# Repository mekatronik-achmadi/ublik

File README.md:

# ublik

Hello everybody out there

I’m doing a free customizable and developer-friendly mini Solar Home System (just a hobby, won’t be big and
professional like many vendors nowadays) 

I’d like any feedback on things people who understand how Solar Home System supposed to be

I call this project as Ublik. This name come from traditional oil lamp used in my country before modern electric lamp replaced it

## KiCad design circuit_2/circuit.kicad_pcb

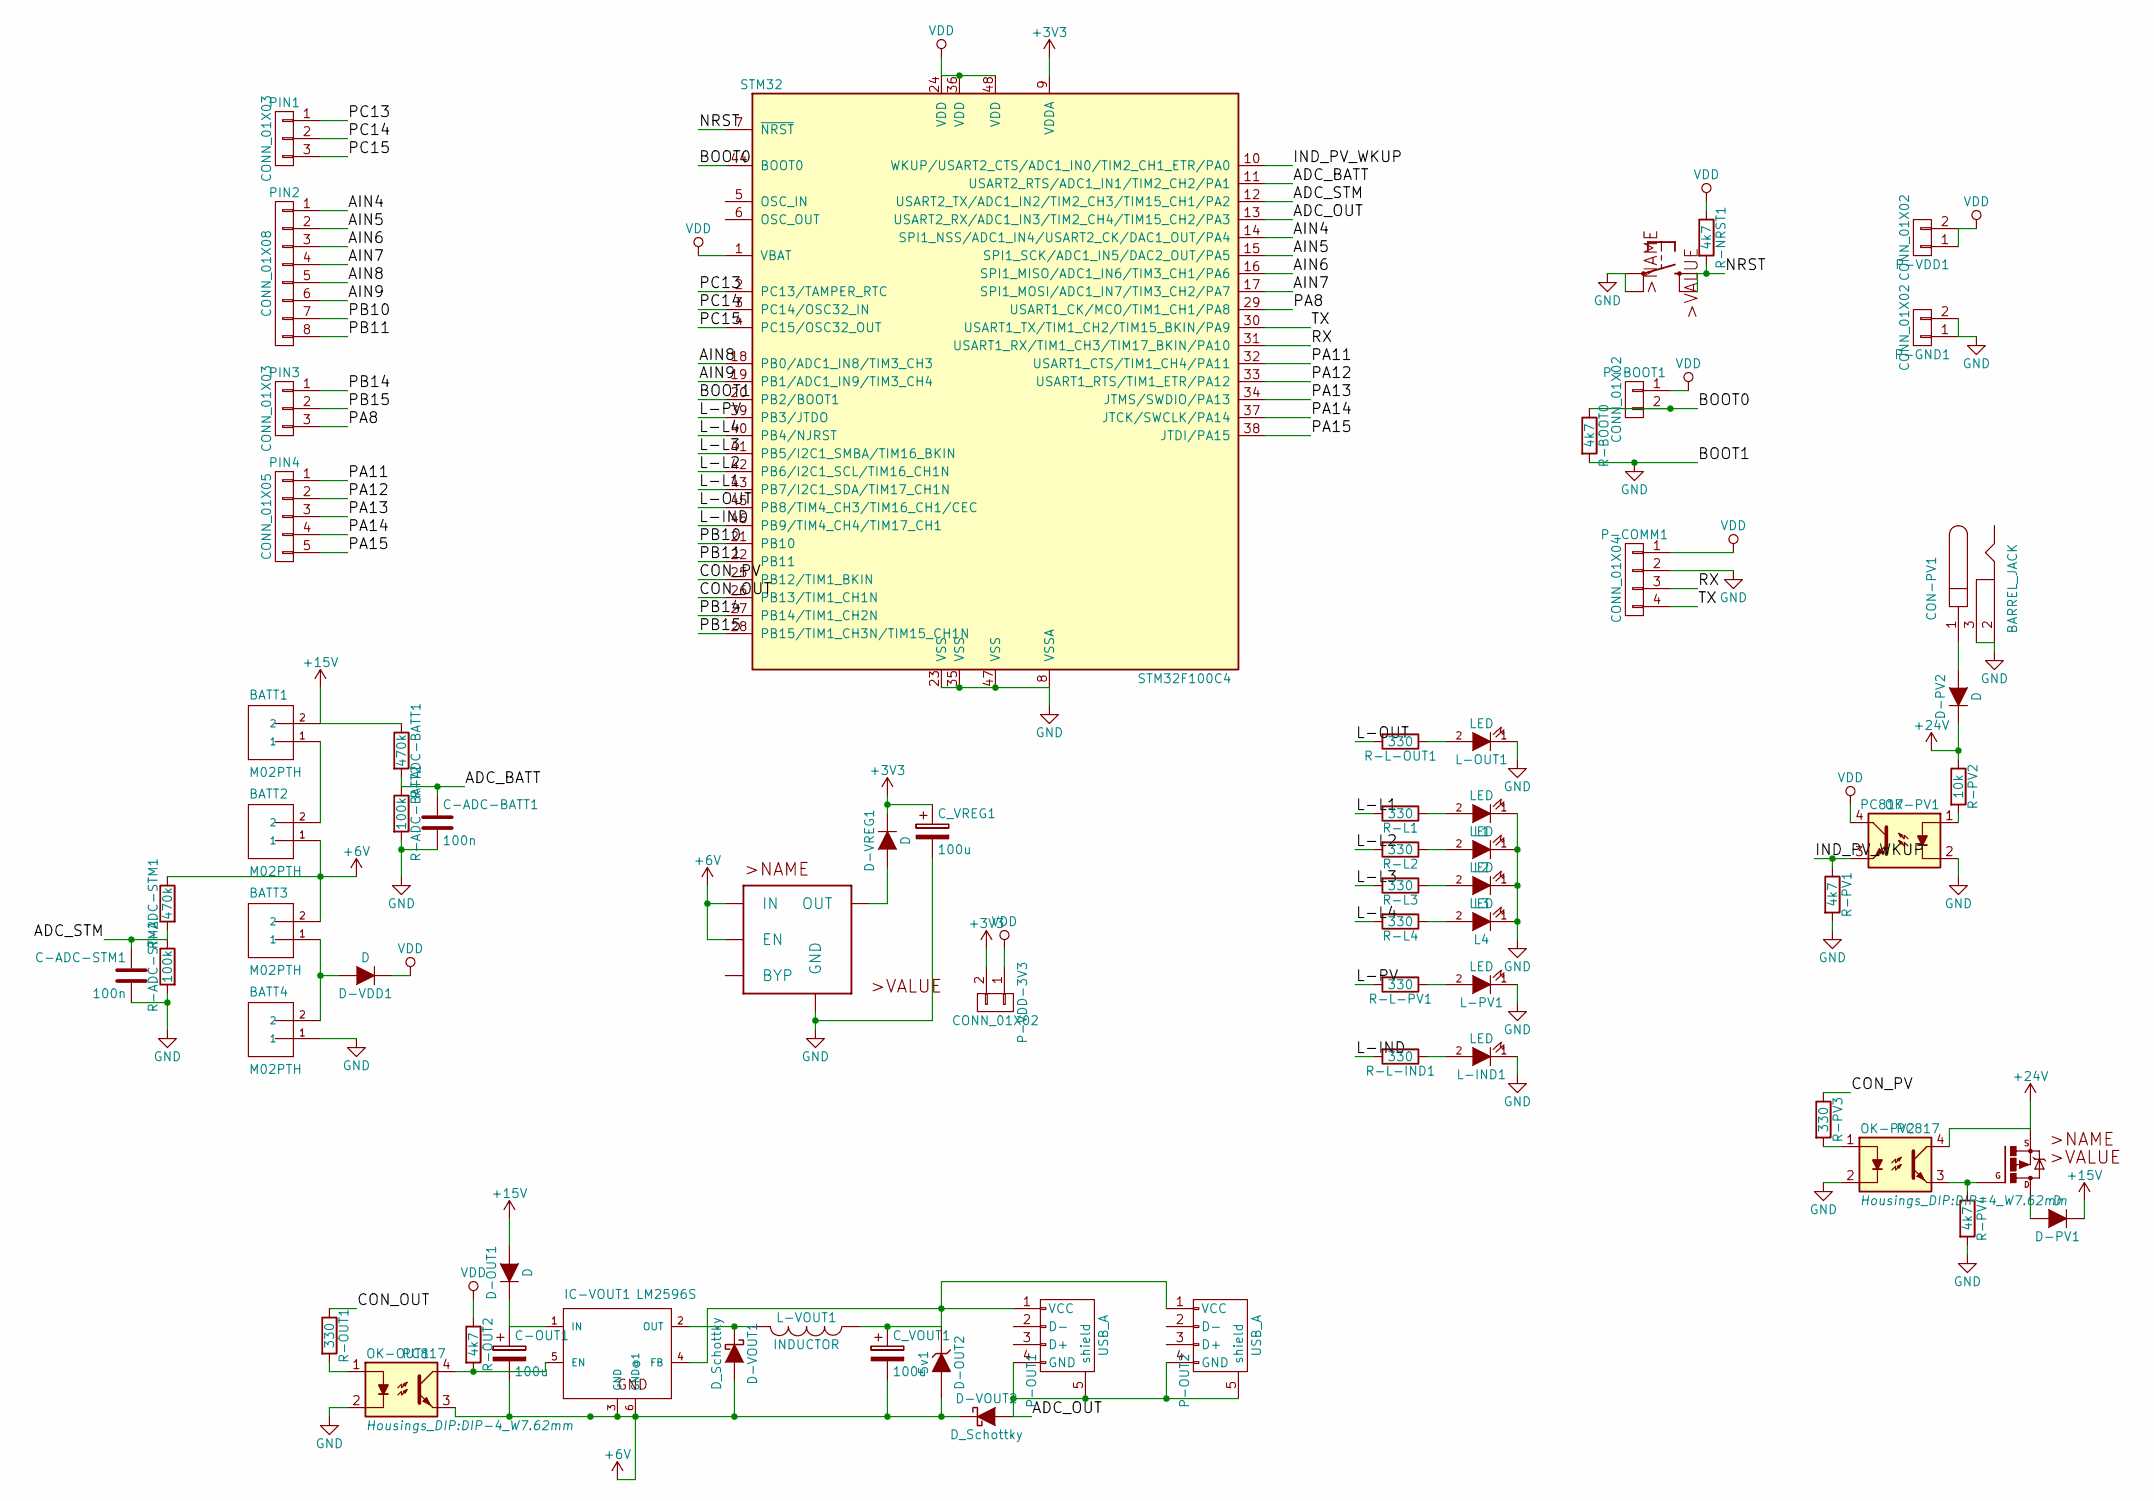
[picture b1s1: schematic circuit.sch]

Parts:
BATT1, BATT2, BATT3, BATT4: M02PTH; SparkFun-1X02_XTRA_BIG
C-ADC-BATT1: 100n; C_0805_HandSoldering
C-ADC-STM1: 100n; C_0805_HandSoldering
C-OUT1: 100u; C_Radial_D5_L6_P2.5
CON-PV1: BARREL_JACK; JACK_ALIM
C_VOUT1: 100u; C_Radial_D5_L6_P2.5
C_VREG1: 100u; C_Radial_D5_L6_P2.5
D-OUT1: D; SMA_Handsoldering
D-OUT2: 5v1; MELF_Handsoldering
D-PV1, D-PV2: D; SMA_Handsoldering
D-VDD1: D; SMA_Handsoldering
D-VOUT1, D-VOUT2: D_Schottky; SMA_Handsoldering
D-VREG1: D; SMA_Handsoldering
IC-VOUT1: LM2596S; TO-263-5Lead
L1, L2, L3, L4: LED; LED-0805
L-IND1: LED; LED-0805
L-OUT1: LED; LED-0805
L-PV1: LED; LED-0805
L-VOUT1: INDUCTOR; INDUCTOR_V
OK-OUT1: PC817; DIP-4_W7.62mm
OK-PV1, OK-PV2: PC817; DIP-4_W7.62mm
P-BOOT1: CONN_01X02; Pin_Header_Straight_1x02
P-COMM1: CONN_01X04; Pin_Header_Straight_1x04
P-GND1: CONN_01X02; Pin_Header_Straight_1x02
P-OUT1, P-OUT2: USB_A
P-VDD1: CONN_01X02; Pin_Header_Straight_1x02
P-VDD-3V3: CONN_01X02; Pin_Header_Straight_1x02
PIN1, PIN3: CONN_01X03; Pin_Header_Straight_1x03
PIN2: CONN_01X08; Pin_Header_Straight_1x08
PIN4: CONN_01X05; Pin_Header_Straight_1x05
R-ADC-BATT1: 470k; R_0805_HandSoldering
R-ADC-BATT2: 100k; R_0805_HandSoldering
R-ADC-STM1: 470k; R_0805_HandSoldering
R-ADC-STM2: 100k; R_0805_HandSoldering
R-BOOT0: 4k7; R_0805_HandSoldering
R-L1, R-L2, R-L3, R-L4: 330; R_0805_HandSoldering
R-L-IND1: 330; R_0805_HandSoldering
R-L-OUT1: 330; R_0805_HandSoldering
R-L-PV1: 330; R_0805_HandSoldering
R-NRST1: 4k7; R_0805_HandSoldering
R-OUT1: 330; R_0805_HandSoldering
R-OUT2: 4k7; R_0805_HandSoldering
R-PV1, R-PV4: 4k7; R_0805_HandSoldering
R-PV2: 10k; R_0805_HandSoldering
R-PV3: 330; R_0805_HandSoldering
STM32: STM32F100C4; TQFP-48_7x7mm_Pitch0.5mm
SW-NRST1: 10-XX_B3F-10XX; B3F-10XX
TR-PV1: IRF9530_TO220BV; D2PACK
U1: MIC5219BM5_SOT23-5; SOT-23-5

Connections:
+3V3: C_VREG1.1, D-VREG1.1 (K), P-VDD-3V3.2, STM32.9 (VDDA)
+6V: BATT2.1, BATT3.2, C-OUT1.2, C_VOUT1.2, D-OUT2.2 (A), D-VOUT1.2 (A), D-VOUT2.1 (K), IC-VOUT1.3 (GND), IC-VOUT1.6 (GND@1), OK-OUT1.3, R-ADC-STM1.1, U1.1 (IN), U1.3 (EN)
+15V: BATT1.2, D-OUT1.2 (A), D-PV1.1 (K), R-ADC-BATT1.1
+24V: D-PV2.1 (K), OK-PV2.4, R-PV2.1, TR-PV1.S
/ADC_BATT: C-ADC-BATT1.1, R-ADC-BATT1.2, R-ADC-BATT2.1, STM32.11 (USART2_RTS/ADC1_IN1/TIM2_CH2/PA1)
/ADC_OUT: D-VOUT2.2 (A), P-OUT1.4 (GND), P-OUT1.5 (shield), P-OUT2.4 (GND), P-OUT2.5 (shield), STM32.13 (USART2_RX/ADC1_IN3/TIM2_CH4/TIM15_CH2/P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)
/ADC_STM: C-ADC-STM1.1, R-ADC-STM1.2, R-ADC-STM2.1, STM32.12 (USART2_TX/ADC1_IN2/TIM2_CH3/TIM15_CH1/P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)
/AIN4: PIN2.1, STM32.14 (SPI1_NSS/ADC1_IN4/USART2_CK/DAC1_OUT/PA4)
/AIN5: PIN2.2, STM32.15 (SPI1_SCK/ADC1_IN5/DAC2_OUT/PA5)
/AIN6: PIN2.3, STM32.16 (SPI1_MISO/ADC1_IN6/TIM3_CH1/PA6)
/AIN7: PIN2.4, STM32.17 (SPI1_MOSI/ADC1_IN7/TIM3_CH2/PA7)
/AIN8: PIN2.5, STM32.18 (PB0/ADC1_IN8/TIM3_CH3)
/AIN9: PIN2.6, STM32.19 (PB1/ADC1_IN9/TIM3_CH4)
/BOOT0: P-BOOT1.2, R-BOOT0.1, STM32.44 (BOOT0)
/CON_OUT: R-OUT1.1, STM32.26 (PB13/TIM1_CH1N)
/CON_PV: R-PV3.1, STM32.25 (PB12/TIM1_BKIN)
/IND_PV_WKUP: OK-PV1.3, R-PV1.1, STM32.10 (WKUP/USART2_CTS/ADC1_IN0/TIM2_CH1_ETR/P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)
/L-IND: R-L-IND1.2, STM32.46 (PB9/TIM4_CH4/TIM17_CH1)
/L-L1: R-L1.2, STM32.43 (PB7/I2C1_SDA/TIM17_CH1N)
/L-L2: R-L2.2, STM32.42 (PB6/I2C1_SCL/TIM16_CH1N)
/L-L3: R-L3.2, STM32.41 (PB5/I2C1_SMBA/TIM16_BKIN)
/L-L4: R-L4.2, STM32.40 (PB4/NJRST)
/L-OUT: R-L-OUT1.2, STM32.45 (PB8/TIM4_CH3/TIM16_CH1/CEC)
/L-PV: R-L-PV1.2, STM32.39 (PB3/JTDO)
/NRST: R-NRST1.2, STM32.7 (~NRST), SW-NRST1.1 (S), SW-NRST1.2 (S1)
/PA8: PIN3.3, STM32.29 (USART1_CK/MCO/TIM1_CH1/PA8)
/PA11: PIN4.1, STM32.32 (USART1_CTS/TIM1_CH4/PA11)
/PA12: PIN4.2, STM32.33 (USART1_RTS/TIM1_ETR/PA12)
/PA13: PIN4.3, STM32.34 (JTMS/SWDIO/PA13)
/PA14: PIN4.4, STM32.37 (JTCK/SWCLK/PA14)
/PA15: PIN4.5, STM32.38 (JTDI/PA15)
/PB10: PIN2.7, STM32.21 (PB10)
/PB11: PIN2.8, STM32.22 (PB11)
/PB14: PIN3.1, STM32.27 (PB14/TIM1_CH2N)
/PB15: PIN3.2, STM32.28 (PB15/TIM1_CH3N/TIM15_CH1N)
/PC13: PIN1.1, STM32.2 (PC13/TAMPER_RTC)
/PC14: PIN1.2, STM32.3 (PC14/OSC32_IN)
/PC15: PIN1.3, STM32.4 (PC15/OSC32_OUT)
/RX: P-COMM1.3, STM32.31 (USART1_RX/TIM1_CH3/TIM17_BKIN/PA10)
/TX: P-COMM1.4, STM32.30 (USART1_TX/TIM1_CH2/TIM15_BKIN/PA9)
GND: BATT4.1, C-ADC-BATT1.2, C-ADC-STM1.2, CON-PV1.2, CON-PV1.3, C_VREG1.2, L1.1 (K), L2.1 (K), L3.1 (K), L4.1 (K), L-IND1.1 (K), L-OUT1.1 (K), L-PV1.1 (K), OK-OUT1.2, OK-PV1.2, OK-PV2.2, P-COMM1.2, P-GND1.1, P-GND1.2, R-ADC-BATT2.2, R-ADC-STM2.2, R-BOOT0.2, R-PV1.2, R-PV4.2, STM32.8 (VSSA), STM32.20 (PB2/BOOT1), STM32.23 (VSS), STM32.35 (VSS), STM32.47 (VSS), SW-NRST1.3, SW-NRST1.4 (P1), U1.2 (GND)
unnamed: BATT1.1, BATT2.2
unnamed: BATT3.1, BATT4.2, D-VDD1.2 (A)
unnamed: C-OUT1.1, D-OUT1.1 (K), IC-VOUT1.1 (IN)
unnamed: CON-PV1.1, D-PV2.2 (A)
unnamed: C_VOUT1.1, D-OUT2.1 (K), IC-VOUT1.4 (FB), L-VOUT1.1, P-OUT1.1 (VCC), P-OUT2.1 (VCC)
unnamed: D-PV1.2 (A), TR-PV1.D
unnamed: D-VOUT1.1 (K), IC-VOUT1.2 (OUT), L-VOUT1.2
unnamed: D-VREG1.2 (A), U1.5 (OUT)
unnamed: IC-VOUT1.5 (EN), OK-OUT1.4, R-OUT2.2
unnamed: L1.2 (A), R-L1.1
unnamed: L2.2 (A), R-L2.1
unnamed: L3.2 (A), R-L3.1
unnamed: L4.2 (A), R-L4.1
unnamed: L-IND1.2 (A), R-L-IND1.1
unnamed: L-OUT1.2 (A), R-L-OUT1.1
unnamed: L-PV1.2 (A), R-L-PV1.1
unnamed: OK-OUT1.1, R-OUT1.2
unnamed: OK-PV1.1, R-PV2.2
unnamed: OK-PV2.1, R-PV3.2
unnamed: OK-PV2.3, R-PV4.1, TR-PV1.G
VDD: D-VDD1.1 (K), OK-PV1.4, P-BOOT1.1, P-COMM1.1, P-VDD1.1, P-VDD1.2, P-VDD-3V3.1, R-NRST1.1, R-OUT2.1, STM32.1 (VBAT), STM32.24 (VDD), STM32.36 (VDD), STM32.48 (VDD)

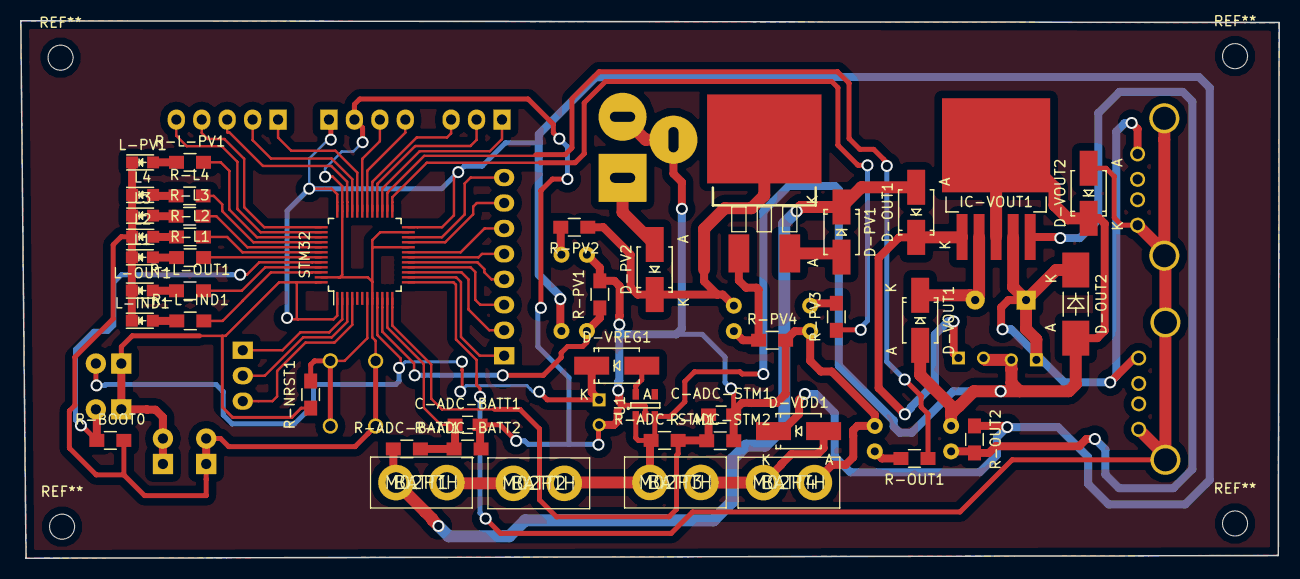
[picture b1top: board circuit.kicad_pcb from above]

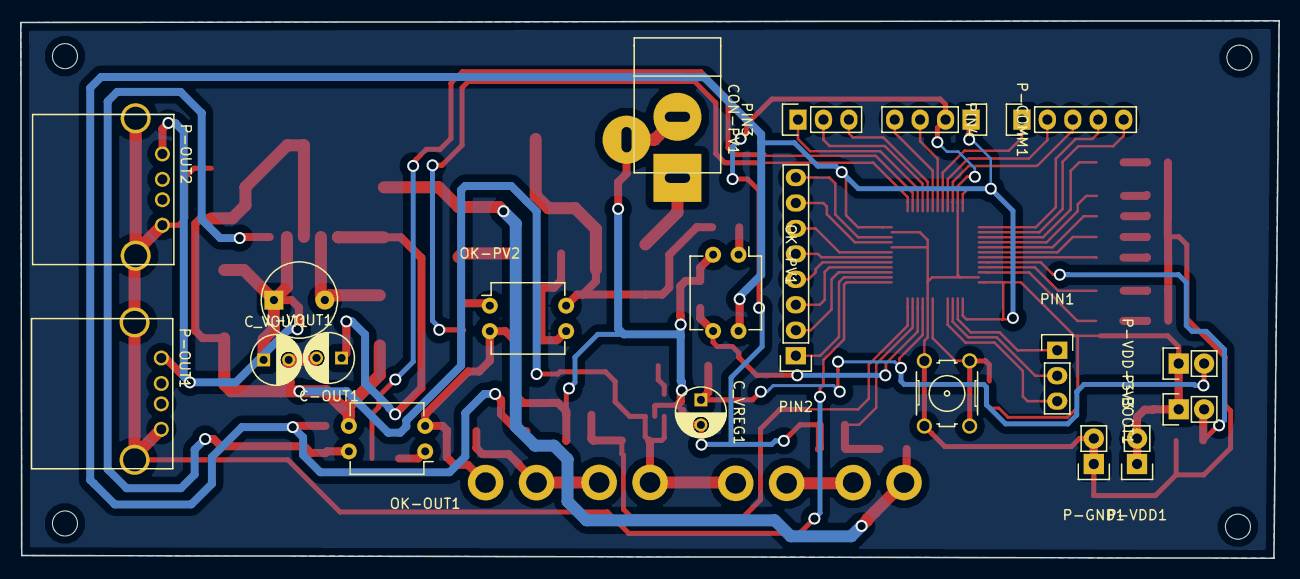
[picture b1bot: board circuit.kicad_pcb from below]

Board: 2 copper layers, 125.6 x 53.6 mm, 64 parts (20 on the bottom side), 62 nets.

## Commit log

2016-04-20 logo added
2016-04-20 logo modified
2016-04-20 logo
2016-04-20 logo resized
2016-04-20 little logo
2016-04-20 tinggal cke batere
2016-04-20 development
2016-04-26 next: testing
2016-04-26 next : test
2016-04-28 add usb feature
2016-04-28 test
2016-04-28 support stm32f100c4
2016-04-29 work on circuit
2016-05-03 circuit building
2016-05-03 tambah test pad
2016-05-03 circuit finish
2016-05-10 circuit fabricated
2016-05-10 standby wake up by sleep RTC
2016-05-11 alarm standby OK
2016-05-11 ready to test again
2016-05-11 Saver feature OK
2016-05-11 Saver Feature Ready
2016-05-12 Saver problem
2016-05-12 tinggal ADC Battery
2016-05-12 Use Stop Mode only
2016-05-12 revised
2016-05-14 list components
2016-05-19 under test
2016-05-20 testing
2016-05-24 stm32f1013 ok
2016-05-24 f100c4 added
2016-05-26 add test sources
2016-05-27 test in progress
2016-05-30 some minor fixed
2016-06-03 revisi minor
2016-06-07 revisi
2016-06-07 aduh pusing
2016-06-08 minor revisi
2016-06-14 proto src
2016-06-14 modified platform
2016-06-14 platform modified
2016-06-20 new design
2016-07-18 firmware fix
2016-09-20 circuit full 5v
2016-10-12 circuit 2
